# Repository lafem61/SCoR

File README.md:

# SCoR
The VHDL code used, Inverse Kinematics code both in MATLAB used for simulation and Java used for Apache Hadoop, and gerber files for the PCB for the project are all posted here.

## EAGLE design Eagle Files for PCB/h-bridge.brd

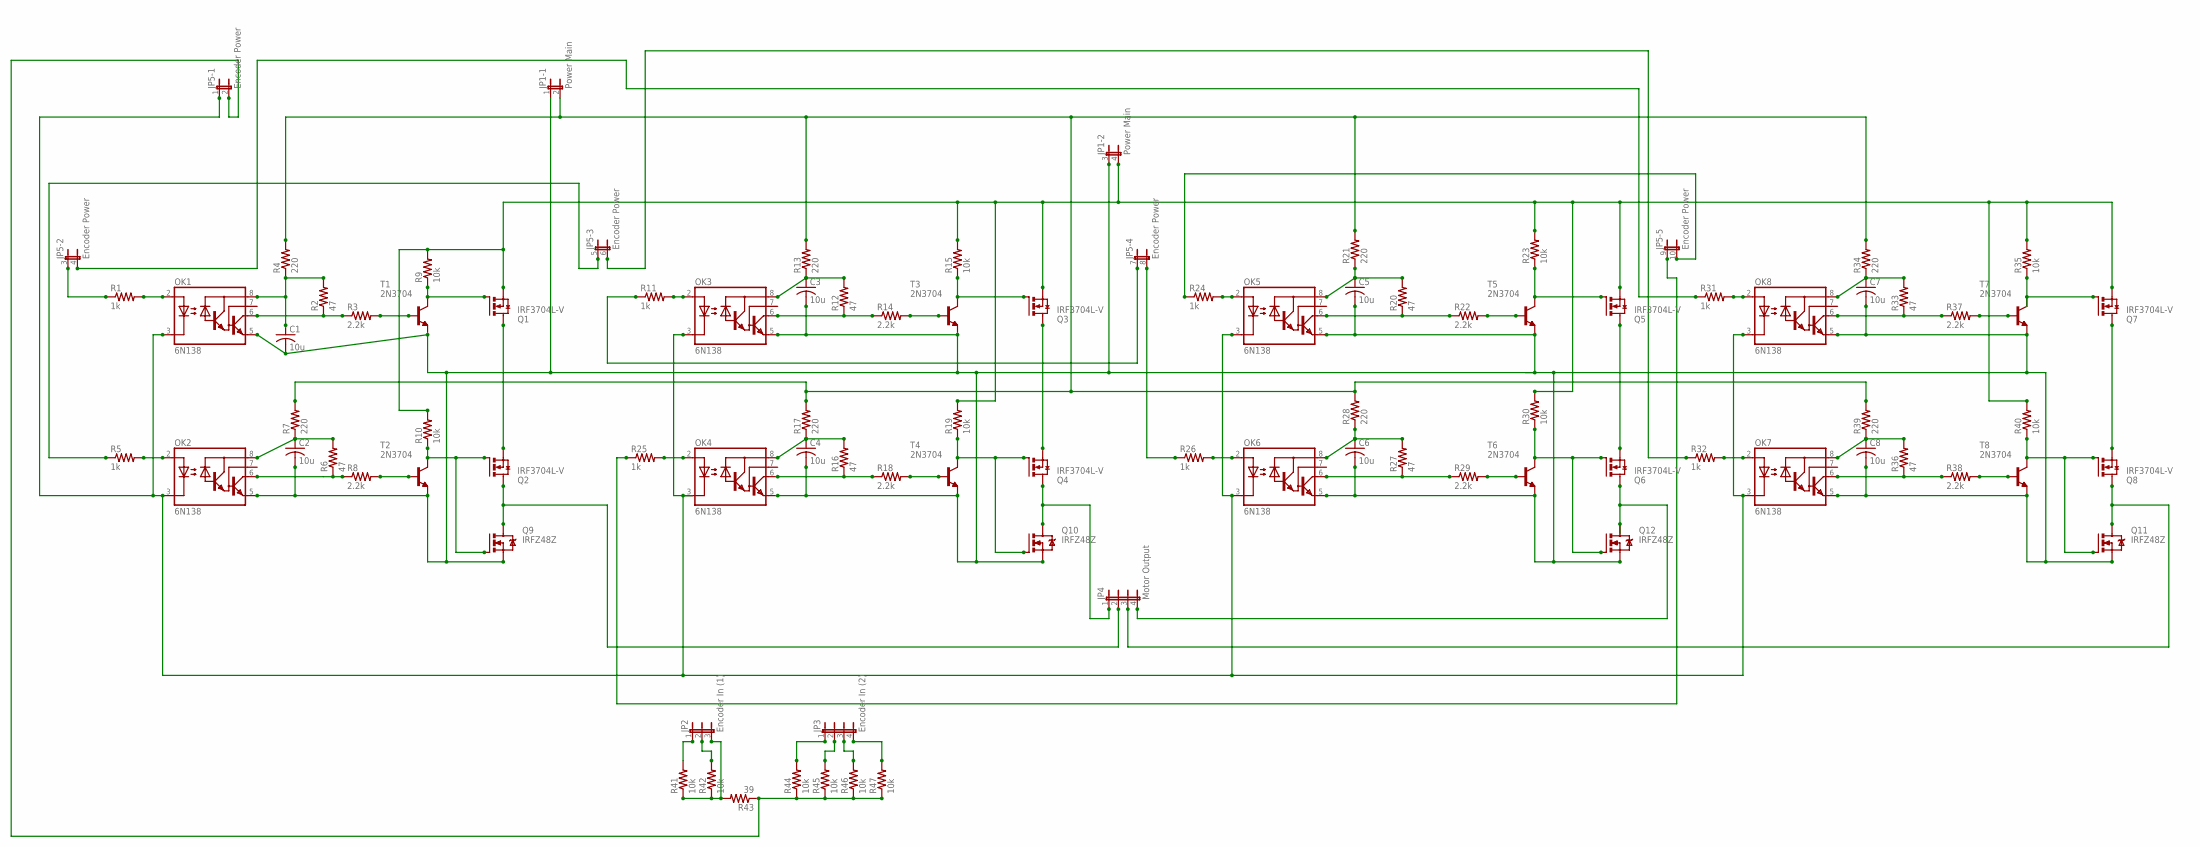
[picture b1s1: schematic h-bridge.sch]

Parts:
C1, C2, C3, C4, C5, C6, C7, C8: 10u; C025-025X050
JP1: Power Main; JP2Q
JP2: Encoder In (1); JP2
JP3: Encoder In (2); JP4
JP4: Motor Output; JP4
JP5: Encoder Power; JP5Q
OK1, OK2, OK3, OK4, OK5, OK6, OK7, OK8: 6N138; DIL08
Q1, Q2, Q3, Q4, Q5, Q6, Q7, Q8: IRF3704L-V; TO262-V
Q9, Q10, Q11, Q12: IRFZ48Z; TO220BH
R1, R5, R11, R24, R25, R26, R31, R32: 1k; 0207/10
R2, R6, R12, R16, R20, R27, R33, R36: 47; 0207/10
R3, R8, R14, R18, R22, R29, R37, R38: 2.2k; 0207/10
R4, R7, R13, R17, R21, R28, R34, R39: 220; 0207/10
R9, R10, R15, R19, R23, R30, R35, R40, R41, R42, R44, R45, R46, R47: 10k; 0207/10
R43: 39; 0207/10
T1, T2, T3, T4, T5, T6, T7, T8: 2N3704; TO92

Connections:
GND: C1.2, C2.2, C3.2, C4.2, C5.2, C6.2, C7.2, C8.2, JP1.1, JP1.3 (1), OK1.5 (GND), OK2.5 (GND), OK3.5 (GND), OK4.5 (GND), OK5.5 (GND), OK6.5 (GND), OK7.5 (GND), OK8.5 (GND), Q9.S, Q10.S, Q11.S, Q12.S, T1.3 (E), T2.3 (E), T3.3 (E), T4.3 (E), T5.3 (E), T6.3 (E), T7.3 (E), T8.3 (E)
unnamed: C1.1, OK1.8 (VCC), R2.2, R4.1
unnamed: JP5.1, OK1.3 (C), OK2.3 (C), OK3.3 (C), OK4.3 (C), OK5.3 (C), OK6.3 (C), OK7.3 (C), OK8.3 (C)
unnamed: Q2.1 (G), Q9.G, R10.1, T2.2 (C)
unnamed: JP1.2, R4.2, R7.2, R13.2, R17.2, R21.2, R28.2, R34.2, R39.2
unnamed: C3.1, OK3.8 (VCC), R12.2, R13.1
unnamed: OK3.6 (VO), R12.1, R14.1
unnamed: OK5.2 (A), R24.2
unnamed: OK6.2 (A), R26.2
unnamed: OK4.2 (A), R25.2
unnamed: OK3.2 (A), R11.2
unnamed: OK1.6 (VO), R2.1, R3.1
unnamed: R3.2, T1.1 (B)
unnamed: Q1.1 (G), R9.1, T1.2 (C)
unnamed: OK1.2 (A), R1.2
unnamed: OK2.2 (A), R5.2
unnamed: JP5.8 (2), R26.1
unnamed: C2.1, OK2.8 (VCC), R6.2, R7.1
unnamed: OK2.6 (VO), R6.1, R8.1
unnamed: R8.2, T2.1 (B)
unnamed: Q1.2 (D), Q2.3 (S)
unnamed: JP4.2, Q2.2 (D), Q9.D
unnamed: R14.2, T3.1 (B)
unnamed: Q3.1 (G), R15.1, T3.2 (C)
unnamed: C4.1, OK4.8 (VCC), R16.2, R17.1
unnamed: JP2.1, R41.2
unnamed: OK4.6 (VO), R16.1, R18.1
unnamed: R18.2, T4.1 (B)
unnamed: Q4.1 (G), Q10.G, R19.1, T4.2 (C)
unnamed: Q3.2 (D), Q4.3 (S)
unnamed: JP4.1, Q4.2 (D), Q10.D
unnamed: C5.1, OK5.8 (VCC), R20.2, R21.1
unnamed: C6.1, OK6.8 (VCC), R27.2, R28.1
unnamed: JP2.2, R42.2
unnamed: JP2.3, R41.1, R42.1, R43.2
unnamed: OK6.6 (VO), R27.1, R29.1
unnamed: OK5.6 (VO), R20.1, R22.1
unnamed: Q5.1 (G), R23.1, T5.2 (C)
unnamed: R22.2, T5.1 (B)
unnamed: R29.2, T6.1 (B)
unnamed: Q6.1 (G), Q12.G, R30.1, T6.2 (C)
unnamed: Q7.2 (D), Q8.3 (S)
unnamed: JP4.4, Q6.2 (D), Q12.D
unnamed: Q5.2 (D), Q6.3 (S)
unnamed: C7.1, OK8.8 (VCC), R33.2, R34.1
unnamed: JP5.2, R43.1, R44.1, R45.1, R46.1, R47.1
unnamed: OK8.6 (VO), R33.1, R37.1
unnamed: C8.1, OK7.8 (VCC), R36.2, R39.1
unnamed: JP3.2, R45.2
unnamed: OK7.6 (VO), R36.1, R38.1
unnamed: R37.2, T7.1 (B)
unnamed: R38.2, T8.1 (B)
unnamed: Q7.1 (G), R35.1, T7.2 (C)
unnamed: Q8.1 (G), Q11.G, R40.1, T8.2 (C)
unnamed: JP3.3, R46.2
unnamed: JP4.3, Q8.2 (D), Q11.D
unnamed: OK8.2 (A), R31.2
unnamed: OK7.2 (A), R32.2
unnamed: JP5.5 (1), R5.1
unnamed: JP5.3 (1), R1.1
unnamed: JP5.9 (1), R25.1
unnamed: JP5.7 (1), R11.1
unnamed: JP5.10 (2), R24.1
unnamed: JP5.6 (2), R32.1
unnamed: JP5.4 (2), R31.1
unnamed: JP1.4 (2), Q1.3 (S), Q3.3 (S), Q5.3 (S), Q7.3 (S), R9.2, R10.2, R15.2, R19.2, R23.2, R30.2, R35.2, R40.2
unnamed: JP3.1, R44.2
unnamed: JP3.4, R47.2

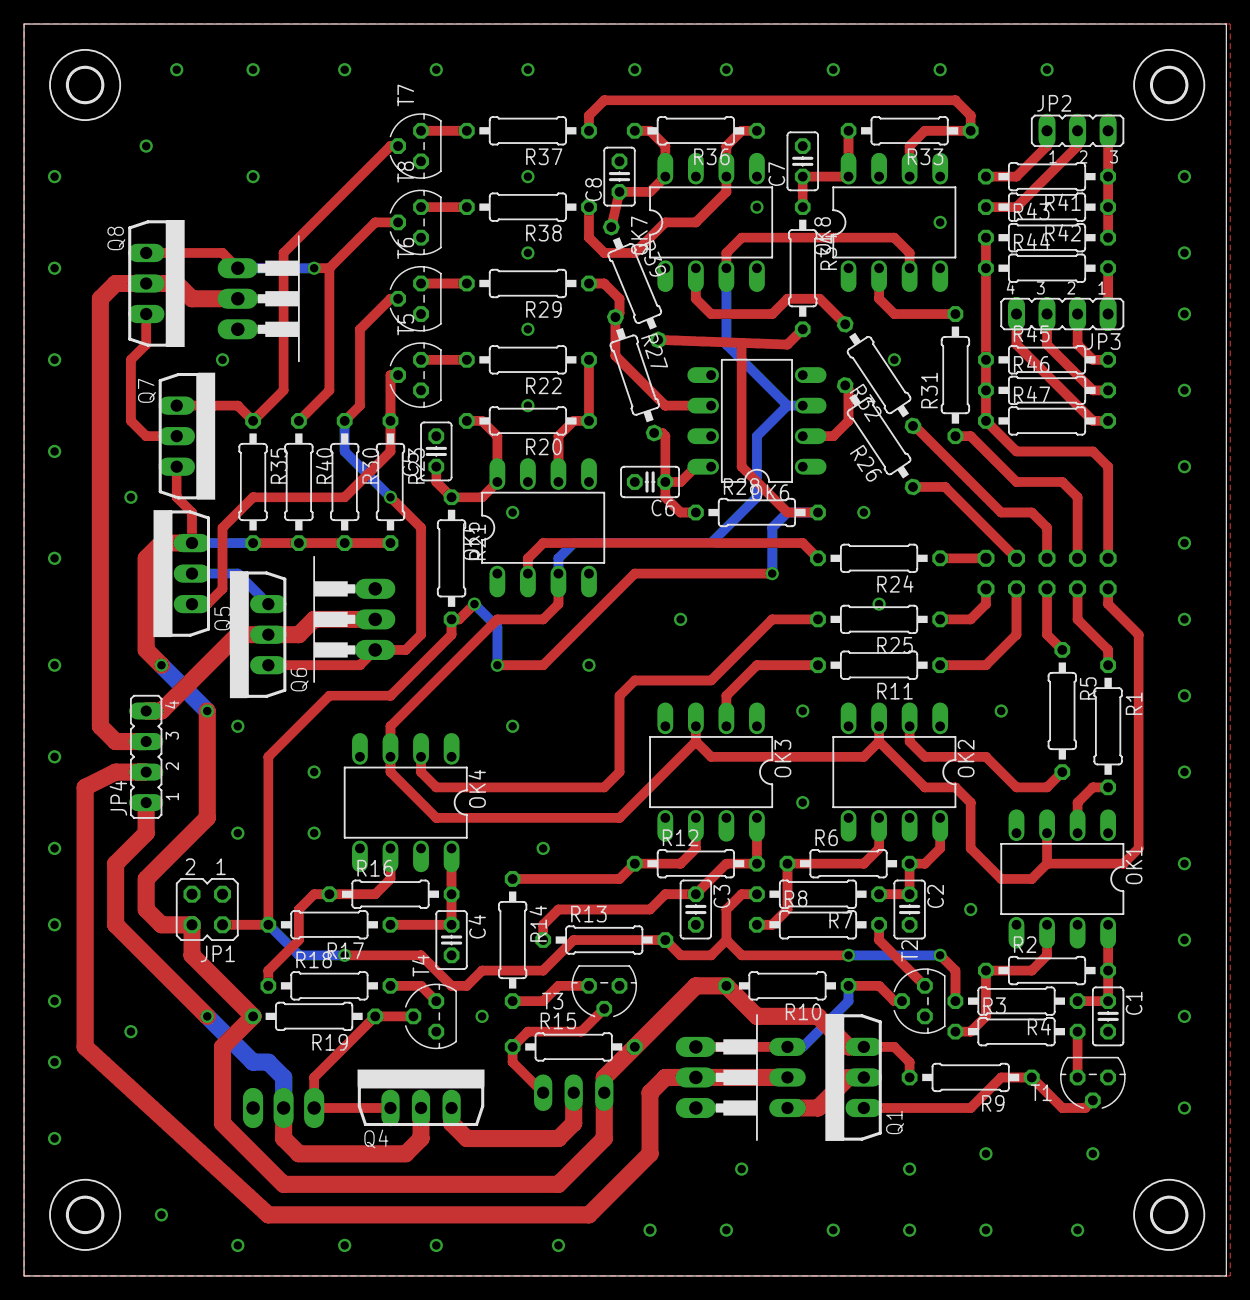
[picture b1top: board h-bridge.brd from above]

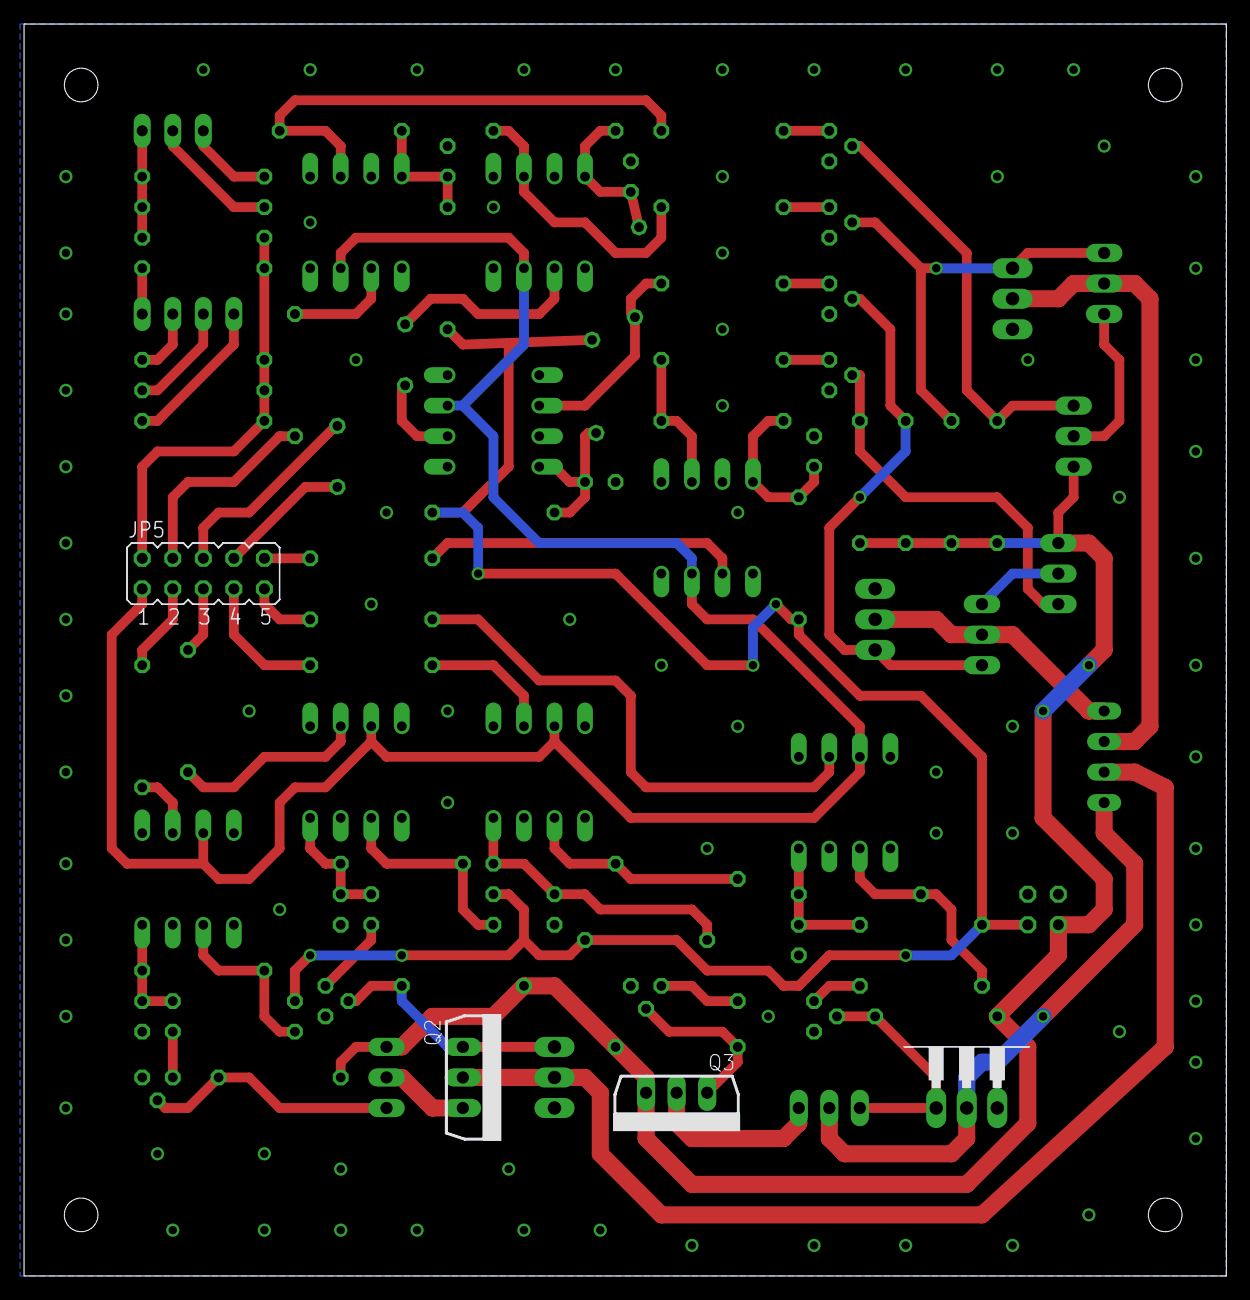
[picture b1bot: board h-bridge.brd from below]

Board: 2 copper layers, 100.0 x 104.1 mm, 92 parts (4 on the bottom side), 68 nets.

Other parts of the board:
U$1, U$2, U$3, U$4: 2,8

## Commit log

2017-04-15 Create Brushless COde
2017-04-15 Create Brushless VHDL code
2017-04-15 Create Brushless VHDL
2017-04-15 Update Brushless VHDL
2017-04-15 Brushless code
